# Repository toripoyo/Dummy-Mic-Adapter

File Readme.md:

# About

Convert Aux/Headphone output to ECM (plug-in power) output.  
You Can add the aux-in(mono) to your smatrphone by using this board and mic/headphone splitter.  

* L/R mix
* Mic Out Gain: -21dB
* Cutoff: 81Hz

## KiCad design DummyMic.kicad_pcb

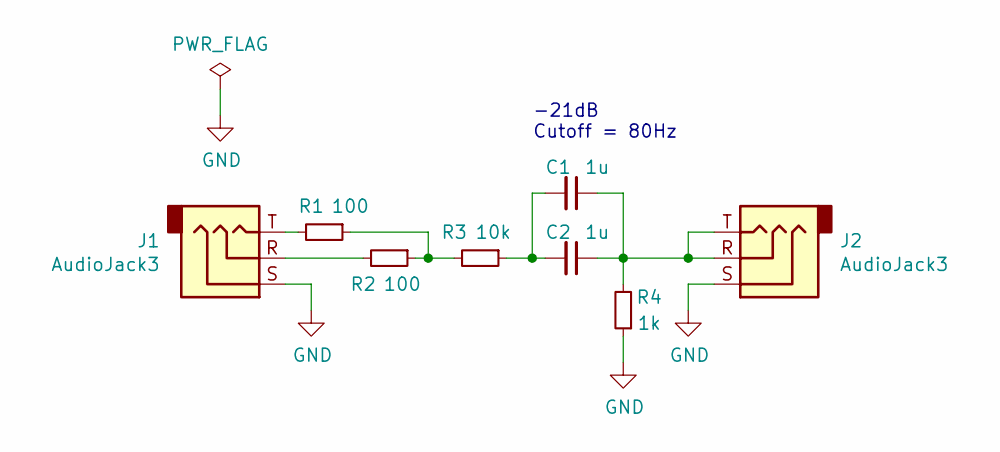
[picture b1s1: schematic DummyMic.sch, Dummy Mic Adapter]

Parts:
C1, C2: 1u; C_0805_2012Metric_Pad1.15x1.40mm_HandSolder
J1, J2: AudioJack3; PJ-3420
R1, R2: 100; R_0603_1608Metric_Pad1.05x0.95mm_HandSolder
R3: 10k; R_0603_1608Metric_Pad1.05x0.95mm_HandSolder
R4: 1k; R_0603_1608Metric_Pad1.05x0.95mm_HandSolder

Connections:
GND: J1.S, J2.S, R4.1
unnamed: C1.1, C2.1, J2.R, J2.T, R4.2
unnamed: C1.2, C2.2, R3.1
unnamed: J1.R, R2.2
unnamed: J1.T, R1.2
unnamed: R1.1, R2.1, R3.2

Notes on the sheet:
-21dB Cutoff = 80Hz

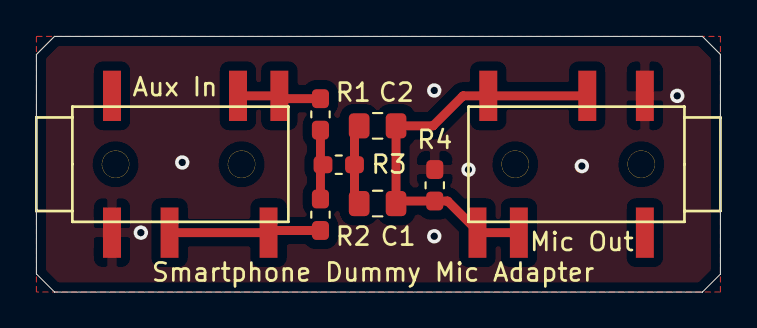
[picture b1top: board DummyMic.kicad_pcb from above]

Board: 2 copper layers, 38.0 x 14.2 mm, 8 parts (0 on the bottom side), 6 nets.

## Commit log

2020-08-24 プロジェクトファイル更新
